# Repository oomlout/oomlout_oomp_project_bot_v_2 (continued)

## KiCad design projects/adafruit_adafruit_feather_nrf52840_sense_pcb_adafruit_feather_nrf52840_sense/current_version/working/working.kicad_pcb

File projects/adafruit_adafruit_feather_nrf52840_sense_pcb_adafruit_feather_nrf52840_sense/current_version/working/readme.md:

# adafruit_feather_nrf52840_sense_pcb
 
## summary 
* id: adafruit_adafruit_feather_nrf52840_sense_pcb_adafruit_feather_nrf52840_sense
* user: adafruit
* name: adafruit_feather_nrf52840_sense_pcb
* board: adafruit_feather_nrf52840_sense
* repo: https://github.com/adafruit/Adafruit-Feather-nRF52840-Sense-PCB

* src_file_repo_sch: 
* src_file_repo_sch_link: https://github.com/adafruit/Adafruit-Feather-nRF52840-Sense-PCB/tree/master/
* full details link: https://github.com/oomlout/oomlout_oomp_project_bot_v_2/tree/main/projects/adafruit_adafruit_feather_nrf52840_sense_pcb_adafruit_feather_nrf52840_sense/current_version/working  

## schematic  
  
[schematic (pdf)](working_schematic.pdf) 

## pcb  

[board (pdf)](working.pdf)  

## working_bom
| Id | Designator | Footprint | Quantity | Designation | Supplier and ref |  | None | 
| --- | --- | --- | --- | --- | --- | --- | --- | 
| 1 | R11,R10 | 0603-NO | 2 | 22 |  |  | [''] | 
| 2 | MDBT1 | MDBT50 | 1 | MDBT50 |  |  | [''] | 
| 3 | U3 | SOT23-5 | 1 | MCP73831T-2ACI/OT |  |  | [''] | 
| 4 | C7,C6,C5,C8,C9 | 0805-NO | 5 | 10uF |  |  | [''] | 
| 5 | U1 | APDS-9960 | 1 | APDS-9960 |  |  | [''] | 
| 6 | X2 | JSTPH2 | 1 | CON_JST_PH_2PIN_MTPH2 |  |  | [''] | 
| 7 | IC4 | SPK0415HM4H | 1 | MIC_PDM |  |  | [''] | 
| 8 | R1 | 0603-NO | 1 | 2.2K |  |  | [''] | 
| 9 | C10,C1,C3,C12,C13 | 0603-NO | 5 | 0.1uF |  |  | [''] | 
| 10 | D1 | SOD-123 | 1 | MBR054 |  |  | [''] | 
| 11 | R4 | 0603-NO | 1 | 4.7K |  |  | [''] | 
| 12 | D3 | CHIPLED_0805_NOOUTLINE | 1 | ORANGE |  |  | [''] | 
| 13 | L1 | _0805MP | 1 | DNP |  |  | [''] | 
| 14 | FID2,FID1 | FIDUCIAL_1MM | 2 | FIDUCIAL_1MM |  |  | [''] | 
| 15 | X1 | 4UCONN_20329_V2 | 1 | 4u20329 |  |  | [''] | 
| 16 | IC1 | LGA16_3X3MM | 1 | LSM6DS33 |  |  | [''] | 
| 17 | U$14 | FEATHERSENSE_TOP | 1 |  |  |  | [''] | 
| 18 | D2 | CHIPLED_0805_NOOUTLINE | 1 | RED |  |  | [''] | 
| 19 | C4 | 0603-NO | 1 | 1uF |  |  | [''] | 
| 20 | U5 | BMP280 | 1 | BMP280 |  |  | [''] | 
| 21 | U4 | SHT3X | 1 | SHT30 |  |  | [''] | 
| 22 | D4 | CHIPLED_0603_NOOUTLINE | 1 | BLUE |  |  | [''] | 
| 23 | SW1,SW2 | BTN_KMR2_4.6X2.8 | 2 | KMR2 |  |  | [''] | 
| 24 | LED1 | LED3535 | 1 | WS2812B3535 |  |  | [''] | 
| 25 | R7 | RESPACK_4X0603 | 1 | 4.7K |  |  | [''] | 
| 26 | Q3 | SOT23-R | 1 | DMG2305 |  |  | [''] | 
| 27 | U2 | SOT23-5 | 1 | AP2112(3.3V) |  |  | [''] | 
| 28 | R3 | 0603-NO | 1 | 1K |  |  | [''] | 
| 29 | IC3 | LGA12_2X2MM | 1 | LIS3MDL |  |  | [''] | 
| 30 | MS1 | FEATHERWING_NODIM | 1 | FEATHERWING_NODIM |  |  | [''] | 
| 31 | IC2 | USON8 | 1 | GD25Q16 |  |  | [''] | 
| 32 | R12 | RESPACK_4X0603 | 1 | 100K |  |  | [''] | 
| 33 | TP1,D-0,D+0 | TP10R | 3 | TPTP10R |  |  | [''] | 
| 34 | SWC0,SWD0 | TP12R | 2 | TPTP12R |  |  | [''] | 
| 35 | U$75 | FEATHERSENSE_BOT | 1 |  |  |  | [''] | 
| 36 | U$10 | PCBFEAT-REV-056 | 1 |  |  |  | [''] | 

## bom_schematic
| Ref | Qnty | Value | Cmp name | Footprint | Description | Vendor | DNP | 
| --- | --- | --- | --- | --- | --- | --- | --- | 
| C1, C3, C10, C12, C13 | 5 | 0.1uF | CAP_CERAMIC0603_NO | working:0603-NO |  |  |  | 
| C4 | 1 | 1uF | CAP_CERAMIC0603_NO | working:0603-NO |  |  |  | 
| C5, C6, C7, C8, C9 | 5 | 10uF | CAP_CERAMIC0805-NOOUTLINE | working:0805-NO |  |  |  | 
| D1 | 1 | MBR054 | DIODE-SCHOTTKYSOD-123 | working:SOD-123 |  |  |  | 
| D2 | 1 | RED | LED0805_NOOUTLINE | working:CHIPLED_0805_NOOUTLINE |  |  |  | 
| D3 | 1 | ORANGE | LED0805_NOOUTLINE | working:CHIPLED_0805_NOOUTLINE |  |  |  | 
| D4 | 1 | BLUE | LED0603_NOOUTLINE | working:CHIPLED_0603_NOOUTLINE |  |  |  | 
| D+0 | 1 | TPTP10R | TPTP10R | working:TP10R |  |  |  | 
| D-0 | 1 | TPTP10R | TPTP10R | working:TP10R |  |  |  | 
| FID1, FID2 | 2 | FIDUCIAL_1MM | FIDUCIAL_1MM | working:FIDUCIAL_1MM |  |  |  | 
| IC1 | 1 | LSM6DS33 | LSM6DS33 | working:LGA16_3X3MM |  |  |  | 
| IC2 | 1 | GD25Q16 | SPIFLASH_8PINUX | working:USON8 |  |  |  | 
| IC3 | 1 | LIS3MDL | LIS3MDL | working:LGA12_2X2MM |  |  |  | 
| IC4 | 1 | MIC_PDM_SPK0415 | MIC_PDM_SPK0415 | working:SPK0415HM4H |  |  |  | 
| L1 | 1 | DNP | INDUCTOR_0805MP | working:_0805MP |  |  |  | 
| LED1 | 1 | WS2812B3535 | WS2812B3535 | working:LED3535 |  |  |  | 
| MDBT1 | 1 | MDBT50 | MDBT50 | working:MDBT50 |  |  |  | 
| MS1 | 1 | FEATHERWING_NODIM | FEATHERWING_NODIM | working:FEATHERWING_NODIM |  |  |  | 
| Q3 | 1 | DMG2305 | MOSFET-P | working:SOT23-R |  |  |  | 
| R1 | 1 | 2.2K | RESISTOR_0603_NOOUT | working:0603-NO |  |  |  | 
| R3 | 1 | 1K | RESISTOR_0603_NOOUT | working:0603-NO |  |  |  | 
| R4 | 1 | 4.7K | RESISTOR_0603_NOOUT | working:0603-NO |  |  |  | 
| R7 | 1 | 4.7K | RESISTOR_4PACK | working:RESPACK_4X0603 |  |  |  | 
| R10, R11 | 2 | 22 | RESISTOR_0603_NOOUT | working:0603-NO |  |  |  | 
| R12 | 1 | 100K | RESISTOR_4PACK | working:RESPACK_4X0603 |  |  |  | 
| SW1, SW2 | 2 | KMR2 | SWITCH_TACT_SMT4.6X2.8 | working:BTN_KMR2_4.6X2.8 |  |  |  | 
| SWC0 | 1 | TPTP12R | TPTP12R | working:TP12R |  |  |  | 
| SWD0 | 1 | TPTP12R | TPTP12R | working:TP12R |  |  |  | 
| TP1 | 1 | TPTP10R | TPTP10R | working:TP10R |  |  |  | 
| U1 | 1 | APDS-9960 | APDS-9960 | working:APDS-9960 |  |  |  | 
| U2 | 1 | AP2112(3.3V) | VREG_SOT23-5 | working:SOT23-5 |  |  |  | 
| U3 | 1 | MCP73831T-2ACI/OT | MCP73831/2 | working:SOT23-5 |  |  |  | 
| U4 | 1 | SHT30 | SHT3X | working:SHT3X |  |  |  | 
| U5 | 1 | BMP280 | BMP280 | working:BMP280 |  |  |  | 
| X1 | 1 | 4u20329 | USB_MICRO_20329_V2 | working:4UCONN_20329_V2 |  |  |  | 
| X2 | 1 | CON_JST_PH_2PIN_MTPH2 | CON_JST_PH_2PIN_MTPH2 | working:JSTPH2 |  |  |  |

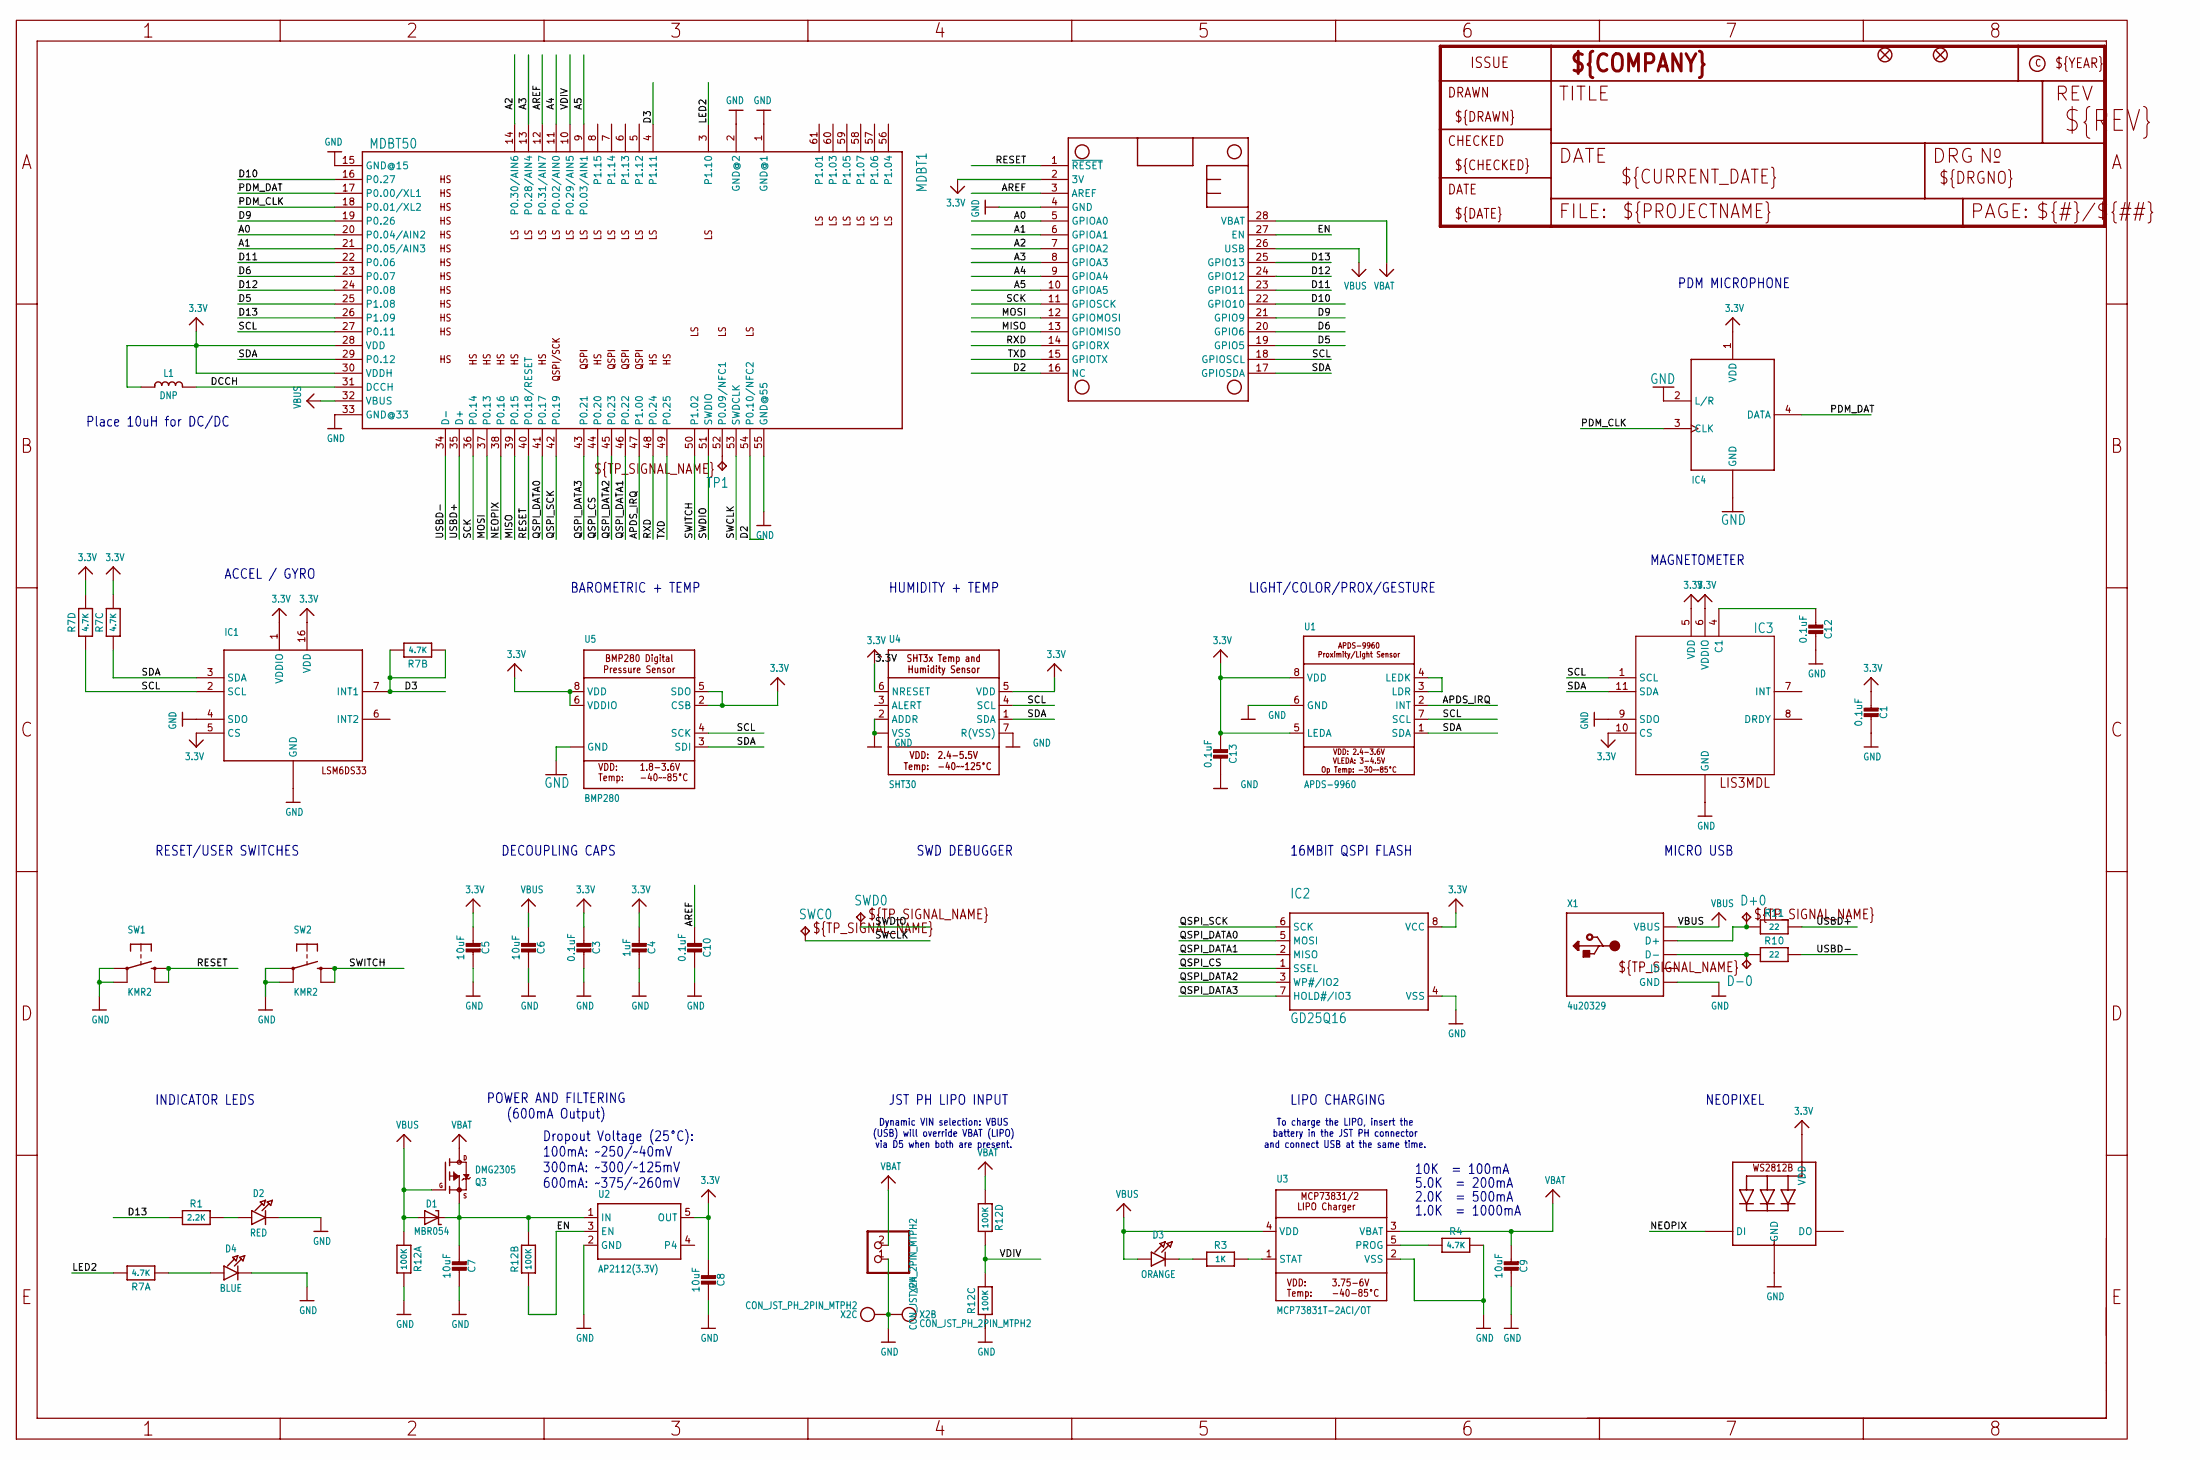
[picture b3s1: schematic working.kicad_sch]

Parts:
C1, C3, C10, C12, C13: 0.1uF; 0603-NO
C4: 1uF; 0603-NO
C5, C6, C7, C8, C9: 10uF; 0805-NO
D1: MBR054; SOD-123
D2: RED; CHIPLED_0805_NOOUTLINE
D3: ORANGE; CHIPLED_0805_NOOUTLINE
D4: BLUE; CHIPLED_0603_NOOUTLINE
D+0: TPTP10R; TP10R
D-0: TPTP10R; TP10R
FID1, FID2: FIDUCIAL_1MM
IC1: LSM6DS33; LGA16_3X3MM
IC2: GD25Q16; USON8
IC3: LIS3MDL; LGA12_2X2MM
IC4: MIC_PDM_SPK0415; SPK0415HM4H
L1: DNP; _0805MP
LED1: WS2812B3535; LED3535
MDBT1: MDBT50
MS1: FEATHERWING_NODIM
Q3: DMG2305; SOT23-R
R1: 2.2K; 0603-NO
R3: 1K; 0603-NO
R4: 4.7K; 0603-NO
R7: 4.7K; RESPACK_4X0603
R10, R11: 22; 0603-NO
R12: 100K; RESPACK_4X0603
SW1, SW2: KMR2; BTN_KMR2_4.6X2.8
SWC0: TPTP12R; TP12R
SWD0: TPTP12R; TP12R
TP1: TPTP10R; TP10R
U1: APDS-9960
U2: AP2112(3.3V); SOT23-5
U3: MCP73831T-2ACI/OT; SOT23-5
U4: SHT30; SHT3X
U5: BMP280
X1: 4u20329; 4UCONN_20329_V2
X2: CON_JST_PH_2PIN_MTPH2; JSTPH2

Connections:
3.3V: C1.2, C3.2, C4.2, C5.2, C8.2, C13.2, IC1.1 (VDDIO), IC1.5 (CS), IC1.16 (VDD), IC2.8 (VCC), IC3.5 (VDD), IC3.6 (VDDIO), IC3.10 (CS), IC4.1 (VDD), L1.1, LED1.2 (VDD), MDBT1.28 (VDD), MDBT1.30 (VDDH), MS1.2 (3V), R7.5 (2), R7.6 (2), U1.5 (LEDA), U1.8 (VDD), U2.5 (OUT), U4.5 (VDD), U4.6 (NRESET), U5.2 (CSB), U5.5 (SDO), U5.6 (VDDIO), U5.8 (VDD)
A0: MDBT1.20 (P0.04/AIN2), MS1.5 (GPIOA0)
A1: MDBT1.21 (P0.05/AIN3), MS1.6 (GPIOA1)
A2: MDBT1.14 (P0.30/AIN6), MS1.7 (GPIOA2)
A3: MDBT1.13 (P0.28/AIN4), MS1.8 (GPIOA3)
A4: MDBT1.11 (P0.02/AIN0), MS1.9 (GPIOA4)
A5: MDBT1.9 (P0.03/AIN1), MS1.10 (GPIOA5)
APDS_IRQ: MDBT1.47 (P1.00), U1.2 (INT)
AREF: C10.2, MDBT1.12 (P0.31/AIN7), MS1.3 (AREF)
CAP1: C12.2, IC3.4 (C1)
D2: MDBT1.54 (P0.10/NFC2), MS1.16 (NC)
D3: IC1.7 (INT1), MDBT1.4 (P1.11), R7.2 (1), R7.7 (2)
D5: MDBT1.25 (P1.08), MS1.19 (GPIO5)
D6: MDBT1.23 (P0.07), MS1.20 (GPIO6)
D9: MDBT1.19 (P0.26), MS1.21 (GPIO9)
D10: MDBT1.16 (P0.27), MS1.22 (GPIO10)
D11: MDBT1.22 (P0.06), MS1.23 (GPIO11)
D12: MDBT1.24 (P0.08), MS1.24 (GPIO12)
D13: MDBT1.26 (P1.09), MS1.25 (GPIO13), R1.1
D+: D+0.TP, R11.1, X1.D+
D-: D-0.TP, R10.1, X1.D-
DCCH: L1.2, MDBT1.31 (DCCH)
EN: MS1.27 (EN), R12.2 (1), U2.3 (EN)
GND: C1.1, C3.1, C4.1, C5.1, C6.1, C7.1, C8.1, C9.1, C10.1, C12.1, C13.1, D2.C, D4.C, IC1.4 (SDO), IC1.8 (GND), IC1.9 (GND), IC1.10 (GND), IC1.11 (GND), IC1.12 (GND), IC1.13 (GND), IC1.15 (GND), IC2.4 (VSS), IC3.2 (GND), IC3.3 (GND), IC3.9 (SDO), IC3.12 (GND), IC4.2 (L/R), IC4.5 (GND), IC4.6 (GND), IC4.7 (GND), IC4.8 (GND), LED1.4 (GND), MDBT1.1 (GND@1), MDBT1.2 (GND@2), MDBT1.15 (GND@15), MDBT1.33 (GND@33), MDBT1.55 (GND@55), MS1.4 (GND), R4.2, R12.3 (1), R12.8 (2), SW1.A, SW1.A' (P1), SW2.A, SW2.A' (P1), U1.6 (GND), U2.2 (GND), U3.2 (VSS), U4.2 (ADDR), U4.7 (R(VSS)), U4.8 (VSS), U4.THERMAL (VSS), U5.1 (GND), U5.7 (GND), X1.BASE@1 (GND), X1.BASE@2 (GND), X1.GND, X1.SPRT@1 (GND), X1.SPRT@2 (GND), X1.SPRT@3 (GND), X1.SPRT@4 (GND), X2.1, X2.NC1, X2.NC2
LED2: MDBT1.3 (P1.10), R7.8 (2)
MISO: MDBT1.39 (P0.15), MS1.13 (GPIOMISO)
MOSI: MDBT1.37 (P0.13), MS1.12 (GPIOMOSI)
unnamed: D3.C, R3.1
unnamed: U1.3 (LDR), U1.4 (LEDK)
unnamed: D4.A, R7.1
unnamed: D2.A, R1.2
unnamed: R3.2, U3.1 (STAT)
unnamed: R4.1, U3.5 (PROG)
NEOPIX: LED1.1 (DI), MDBT1.38 (P0.16)
NFC2: MDBT1.52 (P0.09/NFC1), TP1.TP
PDM_CLK: IC4.3 (CLK), MDBT1.18 (P0.01/XL2)
PDM_DAT: IC4.4 (DATA), MDBT1.17 (P0.00/XL1)
QSPI_CS: IC2.1 (SSEL), MDBT1.44 (P0.20)
QSPI_DATA0: IC2.5 (MOSI), MDBT1.41 (P0.17)
QSPI_DATA1: IC2.2 (MISO), MDBT1.46 (P0.22)
QSPI_DATA2: IC2.3 (WP#/IO2), MDBT1.45 (P0.23)
QSPI_DATA3: IC2.7 (HOLD#/IO3), MDBT1.43 (P0.21)
QSPI_SCK: IC2.6 (SCK), MDBT1.42 (P0.19)
RESET: MDBT1.40 (P0.18/RESET), MS1.1 (~RESET), SW1.B (S), SW1.B' (S1)
RXD: MDBT1.48 (P0.24), MS1.14 (GPIORX)
SCK: MDBT1.36 (P0.14), MS1.11 (GPIOSCK)
SCL: IC1.2 (SCL), IC3.1 (SCL), MDBT1.27 (P0.11), MS1.18 (GPIOSCL), R7.4 (1), U1.7 (SCL), U4.4 (SCL), U5.4 (SCK)
SDA: IC1.3 (SDA), IC3.11 (SDA), MDBT1.29 (P0.12), MS1.17 (GPIOSDA), R7.3 (1), U1.1 (SDA), U4.1 (SDA), U5.3 (SDI)
SWCLK: MDBT1.53 (SWDCLK), SWC0.TP
SWDIO: MDBT1.51 (SWDIO), SWD0.TP
SWITCH: MDBT1.50 (P1.02), SW2.B (S), SW2.B' (S1)
TXD: MDBT1.49 (P0.25), MS1.15 (GPIOTX)
USBD+: MDBT1.35 (D+), R11.2
USBD-: MDBT1.34 (D-), R10.2
VBAT: C9.2, MS1.28 (VBAT), Q3.3 (D), R12.4 (1), U3.3 (VBAT), X2.2
VBUS: C6.2, D1.A, D3.A, MDBT1.32 (VBUS), MS1.26 (USB), Q3.1 (G), R12.1, U3.4 (VDD), X1.VBUS
VDIV: MDBT1.10 (P0.29/AIN5), R12.5 (2), R12.6 (2)
VHI: C7.2, D1.C, Q3.2 (S), R12.7 (2), U2.1 (IN)

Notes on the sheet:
RESET/USER SWITCHES
HUMIDITY + TEMP
LIGHT/COLOR/PROX/GESTURE
ACCEL / GYRO
2.0K = 500mA
Place 10uH for DC/DC
1.0K = 1000mA
To charge the LIPO, insert the battery in the JST PH connector and connect USB at the same time.
JST PH LIPO INPUT
Dropout Voltage (25°C): 100mA: ~250/~40mV 300mA: ~300/~125mV 600mA: ~375/~260mV
SWD DEBUGGER
DECOUPLING CAPS
LIPO CHARGING
5.0K = 200mA
INDICATOR LEDS
10K = 100mA
PDM MICROPHONE
BAROMETRIC + TEMP
MAGNETOMETER
MICRO USB
NEOPIXEL
POWER AND FILTERING (600mA Output)
Dynamic VIN selection: VBUS (USB) will override VBAT (LIPO) via D5 when both are present.
16MBIT QSPI FLASH

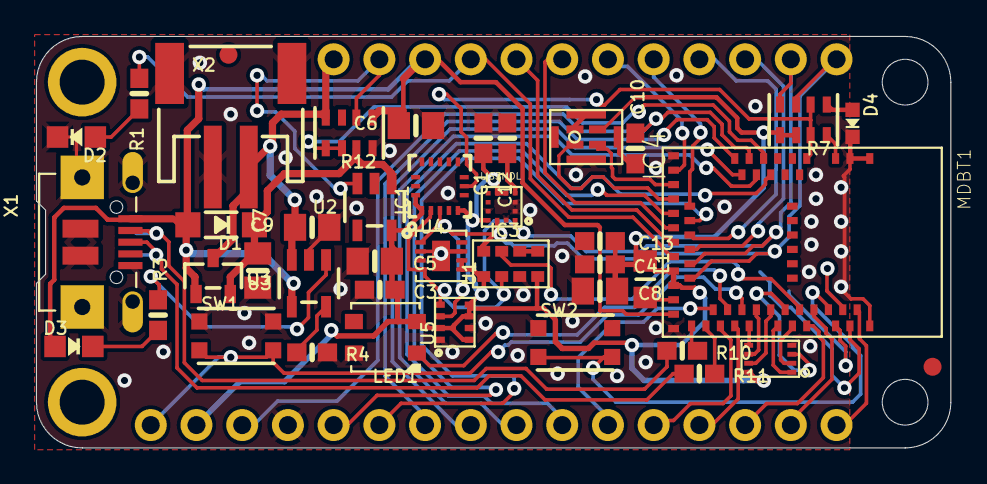
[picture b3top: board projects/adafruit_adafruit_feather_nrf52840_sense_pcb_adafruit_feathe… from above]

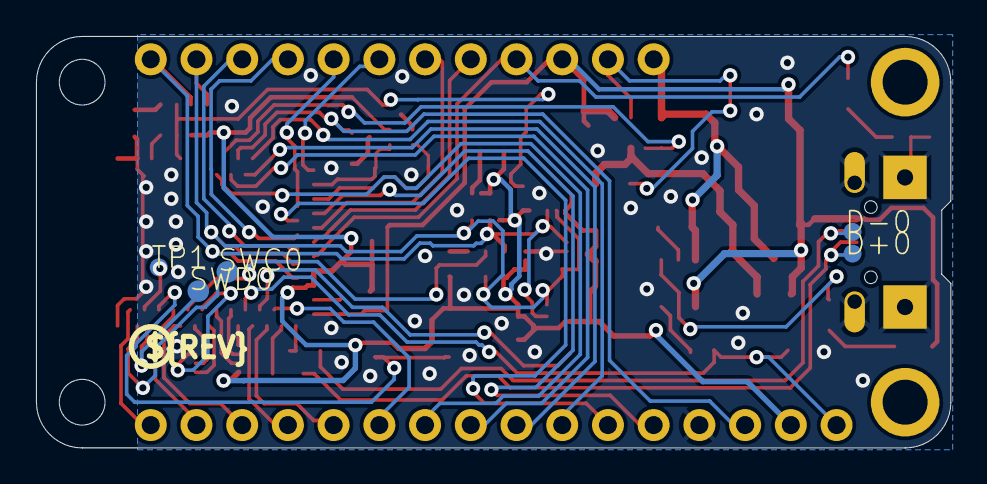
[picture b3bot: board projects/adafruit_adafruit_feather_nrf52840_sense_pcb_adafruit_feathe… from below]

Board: 4 copper layers, 50.8 x 22.9 mm, 50 parts (7 on the bottom side), 58 nets.

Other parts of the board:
U$10: PCBFEAT-REV-056
U$14: FEATHERSENSE_TOP
U$75: FEATHERSENSE_BOT

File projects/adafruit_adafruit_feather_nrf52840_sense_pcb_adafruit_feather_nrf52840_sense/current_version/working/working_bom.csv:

"Id";"Designator";"Footprint";"Quantity";"Designation";"Supplier and ref";
1;"R11,R10";"0603-NO";2;"22";;;
2;"MDBT1";"MDBT50";1;"MDBT50";;;
3;"U3";"SOT23-5";1;"MCP73831T-2ACI/OT";;;
4;"C7,C6,C5,C8,C9";"0805-NO";5;"10uF";;;
5;"U1";"APDS-9960";1;"APDS-9960";;;
6;"X2";"JSTPH2";1;"CON_JST_PH_2PIN_MTPH2";;;
7;"IC4";"SPK0415HM4H";1;"MIC_PDM";;;
8;"R1";"0603-NO";1;"2.2K";;;
9;"C10,C1,C3,C12,C13";"0603-NO";5;"0.1uF";;;
10;"D1";"SOD-123";1;"MBR054";;;
11;"R4";"0603-NO";1;"4.7K";;;
12;"D3";"CHIPLED_0805_NOOUTLINE";1;"ORANGE";;;
13;"L1";"_0805MP";1;"DNP";;;
14;"FID2,FID1";"FIDUCIAL_1MM";2;"FIDUCIAL_1MM";;;
15;"X1";"4UCONN_20329_V2";1;"4u20329";;;
16;"IC1";"LGA16_3X3MM";1;"LSM6DS33";;;
17;"U$14";"FEATHERSENSE_TOP";1;"";;;
18;"D2";"CHIPLED_0805_NOOUTLINE";1;"RED";;;
19;"C4";"0603-NO";1;"1uF";;;
20;"U5";"BMP280";1;"BMP280";;;
21;"U4";"SHT3X";1;"SHT30";;;
22;"D4";"CHIPLED_0603_NOOUTLINE";1;"BLUE";;;
23;"SW1,SW2";"BTN_KMR2_4.6X2.8";2;"KMR2";;;
24;"LED1";"LED3535";1;"WS2812B3535";;;
25;"R7";"RESPACK_4X0603";1;"4.7K";;;
26;"Q3";"SOT23-R";1;"DMG2305";;;
27;"U2";"SOT23-5";1;"AP2112(3.3V)";;;
28;"R3";"0603-NO";1;"1K";;;
29;"IC3";"LGA12_2X2MM";1;"LIS3MDL";;;
30;"MS1";"FEATHERWING_NODIM";1;"FEATHERWING_NODIM";;;
31;"IC2";"USON8";1;"GD25Q16";;;
32;"R12";"RESPACK_4X0603";1;"100K";;;
33;"TP1,D-0,D+0";"TP10R";3;"TPTP10R";;;
34;"SWC0,SWD0";"TP12R";2;"TPTP12R";;;
35;"U$75";"FEATHERSENSE_BOT";1;"";;;
36;"U$10";"PCBFEAT-REV-056";1;"";;;

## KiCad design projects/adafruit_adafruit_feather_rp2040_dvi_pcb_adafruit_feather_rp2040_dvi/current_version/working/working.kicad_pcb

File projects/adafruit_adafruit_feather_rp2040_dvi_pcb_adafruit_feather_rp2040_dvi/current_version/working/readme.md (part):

# adafruit_feather_rp2040_dvi_pcb
 
## summary 
* id: adafruit_adafruit_feather_rp2040_dvi_pcb_adafruit_feather_rp2040_dvi
* user: adafruit
* name: adafruit_feather_rp2040_dvi_pcb
* board: adafruit_feather_rp2040_dvi
* repo: https://github.com/adafruit/Adafruit-Feather-RP2040-DVI-PCB

* src_file_repo_sch: 
* src_file_repo_sch_link: https://github.com/adafruit/Adafruit-Feather-RP2040-DVI-PCB/tree/main/
* full details link: https://github.com/oomlout/oomlout_oomp_project_bot_v_2/tree/main/projects/adafruit_adafruit_feather_rp2040_dvi_pcb_adafruit_feather_rp2040_dvi/current_version/working  

## schematic  
  
[schematic (pdf)](working_schematic.pdf) 

## pcb  

[board (pdf)](working.pdf)  

## working_bom
| Id | Designator | Footprint | Quantity | Designation | Supplier and ref |  | None | 
| --- | --- | --- | --- | --- | --- | --- | --- | 
| 1 | LED1 | SK6805_1515 | 1 | WS2812B_SK6805_1515 |  |  | [''] | 
| 2 | PLABEL25 | PLABEL25 | 1 |  |  |  | [''] | 
| 3 | PLABEL9 | PLABEL9 | 1 |  |  |  | [''] | 
| 4 | PLABEL23 | PLABEL23 | 1 |  |  |  | [''] | 
| 5 | C13,C18,C14,C6,C12,C9,C7 | _0402NO | 7 | 0.1uF |  |  | [''] | 
| 6 | D3 | SOD-323F | 1 | 1N4148 |  |  | [''] | 
| 7 | PLABEL12 | PLABEL12 | 1 |  |  |  | [''] | 
| 8 | R20,R18,R3,R7,R19,R1,R2,R4,R5,R21 | _0402NO | 10 | 10K |  |  | [''] | 
| 9 | R10,R9 | _0402NO | 2 | 22 ohm |  |  | [''] | 
| 10 | C5,C1,C4,C20,C19 | 0805-NO | 5 | 10uF |  |  | [''] | 
| 11 | SW1,SW2 | BTN_RKB2_4.6X2.8 | 2 | KMR2 |  |  | [''] | 
| 12 | C10,C17,C11,C15,C21,C8 | _0402NO | 6 | 1uF |  |  | [''] | 
| 13 | PLABEL22 | PLABEL22 | 1 |  |  |  | [''] | 
| 14 | PLABEL29 | PLABEL29 | 1 |  |  |  | [''] | 
| 15 | PLABEL30 | PLABEL30 | 1 |  |  |  | [''] | 
| 16 | PLABEL32 | PLABEL32 | 1 |  |  |  | [''] | 
| 17 | U$31,U$32 | MOUNTINGHOLE_2.5_PLATED | 2 | MOUNTINGHOLE2.5 |  |  | [''] | 
| 18 | D4 | SOD-323F | 1 | PMEG2020AEA |  |  | [''] | 
| 19 | UTIL0,CEC0 | 1X01_ROUND | 2 |  |  |  | [''] | 
| 20 | PLABEL31 | PLABEL31 | 1 |  |  |  | [''] | 
| 21 | R14,R15 | RESPACK_4X0603 | 2 | 220 Pack |  |  | [''] | 
| 22 | PLABEL35 | PLABEL35 | 1 |  |  |  | [''] | 
| 23 | JP3 | 1X12_ROUND | 1 |  |  |  | [''] | 
| 24 | R8,R13,R12 | _0402NO | 3 | 5.1K |  |  | [''] | 
| 25 | @HOLE0,@HOLE1 |  | 2 |  |  |  | [''] | 
| 26 | PLABEL27 | PLABEL27 | 1 |  |  |  | [''] | 
| 27 | PLABEL11 | PLABEL11 | 1 |  |  |  | [''] | 
| 28 | PLABEL4 | PLABEL4 | 1 |  |  |  | [''] | 
| 29 | U2 | SOT23-5 | 1 | RT9080-3.3 |  |  | [''] | 
| 30 | PLABEL5 | PLABEL5 | 1 |  |  |  | [''] | 
| 31 | PLABEL19 | PLABEL19 | 1 |  |  |  | [''] | 
| 32 | PLABEL28 | PLABEL28 | 1 |  |  |  | [''] | 
| 33 | PLABEL33 | PLABEL33 | 1 |  |  |  | [''] | 
| 34 | L0 | CHIPLED_0603_NOOUTLINE | 1 | RED |  |  | [''] | 
| 35 | PLABEL2 | PLABEL2 | 1 |  |  |  | [''] | 
| 36 | PLABEL3 | PLABEL3 | 1 |  |  |  | [''] | 
| 37 | PLABEL20 | PLABEL20 | 1 |  |  |  | [''] | 
| 38 | PLABEL34 | PLABEL34 | 1 |  |  |  | [''] | 
| 39 | PLABEL14 | PLABEL14 | 1 |  |  |  | [''] | 
| 40 | PLABEL17 | PLABEL17 | 1 |  |  |  | [''] | 
| 41 | R11,R6 | _0402NO | 2 | 1K |  |  | [''] | 
| 42 | PLABEL0 | PLABEL0 | 1 |  |  |  | [''] | 
| 43 | C2,C3 | _0402NO | 2 | 22pF |  |  | [''] | 
| 44 | R16,R17 | _0402NO | 2 | 100K |  |  | [''] | 
| 45 | PLABEL13 | PLABEL13 | 1 |  |  |  | [''] | 
| 46 | PLABEL8 | PLABEL8 | 1 |  |  |  | [''] | 
| 47 | U$35,U$34 | FIDUCIAL_1MM | 2 | FIDUCIAL_1MM |  |  | [''] | 
| 48 | X2 | HDMI_MOLEX_47151-0001 | 1 | 47151-0001 |  |  | [''] | 
| 49 | PLABEL1 | PLABEL1 | 1 |  |  |  | [''] | 
| 50 | PLABEL21 | PLABEL21 | 1 |  |  |  | [''] | 
| 51 | U3 | SOT23-5 | 1 | MCP73831T-2ACI/OT |  |  | [''] | 
| 52 | CONN1 | JST_SH4_RA | 1 | STEMMA_I2C_QTRA |  |  | [''] | 
| 53 | Q2 | SOT363 | 1 | BSS138 |  |  | [''] | 
| 54 | Y1 | CRYSTAL_2.5X2 | 1 | 12MHz/12pF |  |  | [''] | 
| 55 | JP1 | 1X16_ROUND | 1 |  |  |  | [''] | 
| 56 | PLABEL15 | PLABEL15 | 1 |  |  |  | [''] | 
| 57 | Q3 | DFN2015-3 | 1 | DMG3415UFY |  |  | [''] | 
| 58 | IC1 | QFN56_7MM_REDUCEDEPAD | 1 | RP2040_QFN56 |  |  | [''] | 
| 59 | PLABEL24 | PLABEL24 | 1 |  |  |  | [''] | 
| 60 | PLABEL18 | PLABEL18 | 1 |  |  |  | [''] | 
| 61 | PLABEL6 | PLABEL6 | 1 |  |  |  | [''] | 
| 62 | PLABEL10 | PLABEL10 | 1 |  |  |  | [''] | 
| 63 | U1 | USON8_4X4 | 1 | 8MB QSPI |  |  | [''] | 
| 64 | PLABEL7 | PLABEL7 | 1 |  |  |  | [''] | 
| 65 | X6 | USB_C_CUSB31-CFM2AX-01-X | 1 | USB Type C |  |  | [''] | 
| 66 | PLABEL26 | PLABEL26 | 1 |  |  |  | [''] | 
| 67 | PLABEL16 | PLABEL16 | 1 |  |  |  | [''] | 
| 68 | X1 | JSTPH2_BATT | 1 | JSTPH |  |  | [''] | 
| 69 | CHG0 | CHIPLED_0603_NOOUTLINE | 1 | ORANGE |  |  | [''] | 
| 70 | PLABEL49 | PLABEL49 | 1 |  |  |  | [''] | 
| 71 | PLABEL59 | PLABEL59 | 1 |  |  |  | [''] | 
| 72 | PLABEL51 | PLABEL51 | 1 |  |  |  | [''] | 
| 73 | PLABEL40 | PLABEL40 | 1 |  |  |  | [''] | 
| 74 | PLABEL61 | PLABEL61 | 1 |  |  |  | [''] | 
| 75 | PLABEL44 | PLABEL44 | 1 |  |  |  | [''] | 
| 76 | PLABEL65 | PLABEL65 | 1 |  |  |  | [''] | 
| 77 | PLABEL58 | PLABEL58 | 1 |  |  |  | [''] | 
| 78 | PLABEL36 | PLABEL36 | 1 |  |  |  | [''] | 
| 79 | PLABEL67 | PLABEL67 | 1 |  |  |  | [''] | 
| 80 | U$42 | FEATHERLOGO_MED | 1 |  |  |  | [''] | 
| 81 | PLABEL37 | PLABEL37 | 1 |  |  |  | [''] | 
| 82 | PLABEL56 | PLABEL56 | 1 |  |  |  | [''] | 
| 83 | PLABEL60 | PLABEL60 | 1 |  |  |  | [''] | 
| 84 | D+1,D-1 | B1,27 | 2 | TPB1,27 |  |  | [''] | 
| 85 | PLABEL66 | PLABEL66 | 1 |  |  |  | [''] | 
| 86 | PLABEL62 | PLABEL62 | 1 |  |  |  | [''] | 
| 87 | PLABEL45 | PLABEL45 | 1 |  |  |  | [''] | 
| 88 | PLABEL54 | PLABEL54 | 1 |  |  |  | [''] | 
| 89 | PLABEL48 | PLABEL48 | 1 |  |  |  | [''] | 
| 90 | PLABEL38 | PLABEL38 | 1 |  |  |  | [''] | 
| 91 | U$13 | PCBFEAT-REV-040 | 1 |  |  |  | [''] | 
| 92 | PLABEL42 | PLABEL42 | 1 |  |  |  | [''] | 
| 93 | U$46 | ADAFRUIT_5MM | 1 |  |  |  | [''] | 
| 94 | PLABEL50 | PLABEL50 | 1 |  |  |  | [''] | 
| 95 | PLABEL57 | PLABEL57 | 1 |  |  |  | [''] | 
| 96 | TP3 | TESTPOINT_ROUND_1.5MM_NO | 1 |  |  |  | [''] | 
| 97 | PLABEL55 | PLABEL55 | 1 |  |  |  | [''] | 
| 98 | PLABEL46 | PLABEL46 | 1 |  |  |  | [''] | 
| 99 | PLABEL64 | PLABEL64 | 1 |  |  |  | [''] | 
| 100 | PLABEL47 | PLABEL47 | 1 |  |  |  | [''] | 
| 101 | PLABEL53 | PLABEL53 | 1 |  |  |  | [''] | 
| 102 | PLABEL39 | PLABEL39 | 1 |  |  |  | [''] | 
| 103 | PLABEL52 | PLABEL52 | 1 |  |  |  | [''] | 
| 104 | PLABEL43 | PLABEL43 | 1 |  |  |  | [''] | 
| 105 | PLABEL63 | PLABEL63 | 1 |  |  |  | [''] | 
| 106 | PLABEL41 | PLABEL41 | 1 |  |  |  | [''] | 

## bom_schematic
| Ref | Qnty | Value | Cmp name | Footprint | Description | Vendor | DNP | 
| --- | --- | --- | --- | --- | --- | --- | --- | 
| C1, C4, C5, C19, C20 | 5 | 10uF | CAP_CERAMIC0805-NOOUTLINE | working:0805-NO |  |  |  | 
| C2, C3 | 2 | 22pF | CAP_CERAMIC_0402NO | working:_0402NO |  |  |  | 
| C6, C7, C9, C12, C13, C14, C18 | 7 | 0.1uF | CAP_CERAMIC_0402NO | working:_0402NO |  |  |  | 
| C8, C10, C11, C15, C17, C21 | 6 | 1uF | CAP_CERAMIC_0402NO | working:_0402NO |  |  |  | 
| CEC0 | 1 | HEADER-1X1ROUND | HEADER-1X1ROUND | working:1X01_ROUND |  |  |  | 
| CHG0 | 1 | ORANGE | LED0603_NOOUTLINE | working:CHIPLED_0603_NOOUTLINE |  |  |  | 
| CONN1 | 1 | STEMMA_I2C_QTRA | STEMMA_I2C_QTRA | working:JST_SH4_RA |  |  |  | 
| D3 | 1 | 1N4148 | DIODESOD-323F | working:SOD-323F |  |  |  | 
| D4 | 1 | PMEG2020AEA | DIODESOD-323F | working:SOD-323F |  |  |  | 
| D+1 | 1 | TPB1,27 | TPB1,27 | working:B1,27 |  |  |  | 
| D-1 | 1 | TPB1,27 | TPB1,27 | working:B1,27 |  |  |  | 
| IC1 | 1 | RP2040_QFN56 | RP2040_QFN56 | working:QFN56_7MM_REDUCEDEPAD |  |  |  | 
| JP1 | 1 | HEADER-1X16ROUND | HEADER-1X16ROUND | working:1X16_ROUND |  |  |  | 
| JP3 | 1 | HEADER-1X12 | HEADER-1X12 | working:1X12_ROUND |  |  |  | 
| L0 | 1 | RED | LED0603_NOOUTLINE | working:CHIPLED_0603_NOOUTLINE |  |  |  | 
| LED1 | 1 | WS2812B_SK6805_1515 | WS2812B_SK6805_1515 | working:SK6805_1515 |  |  |  | 
| Q2 | 1 | BSS138 | MOSFET-N_DUAL | working:SOT363 |  |  |  | 
| Q3 | 1 | DMG3415UFY | MOSFET-P_DFN2015 | working:DFN2015-3 |  |  |  | 
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
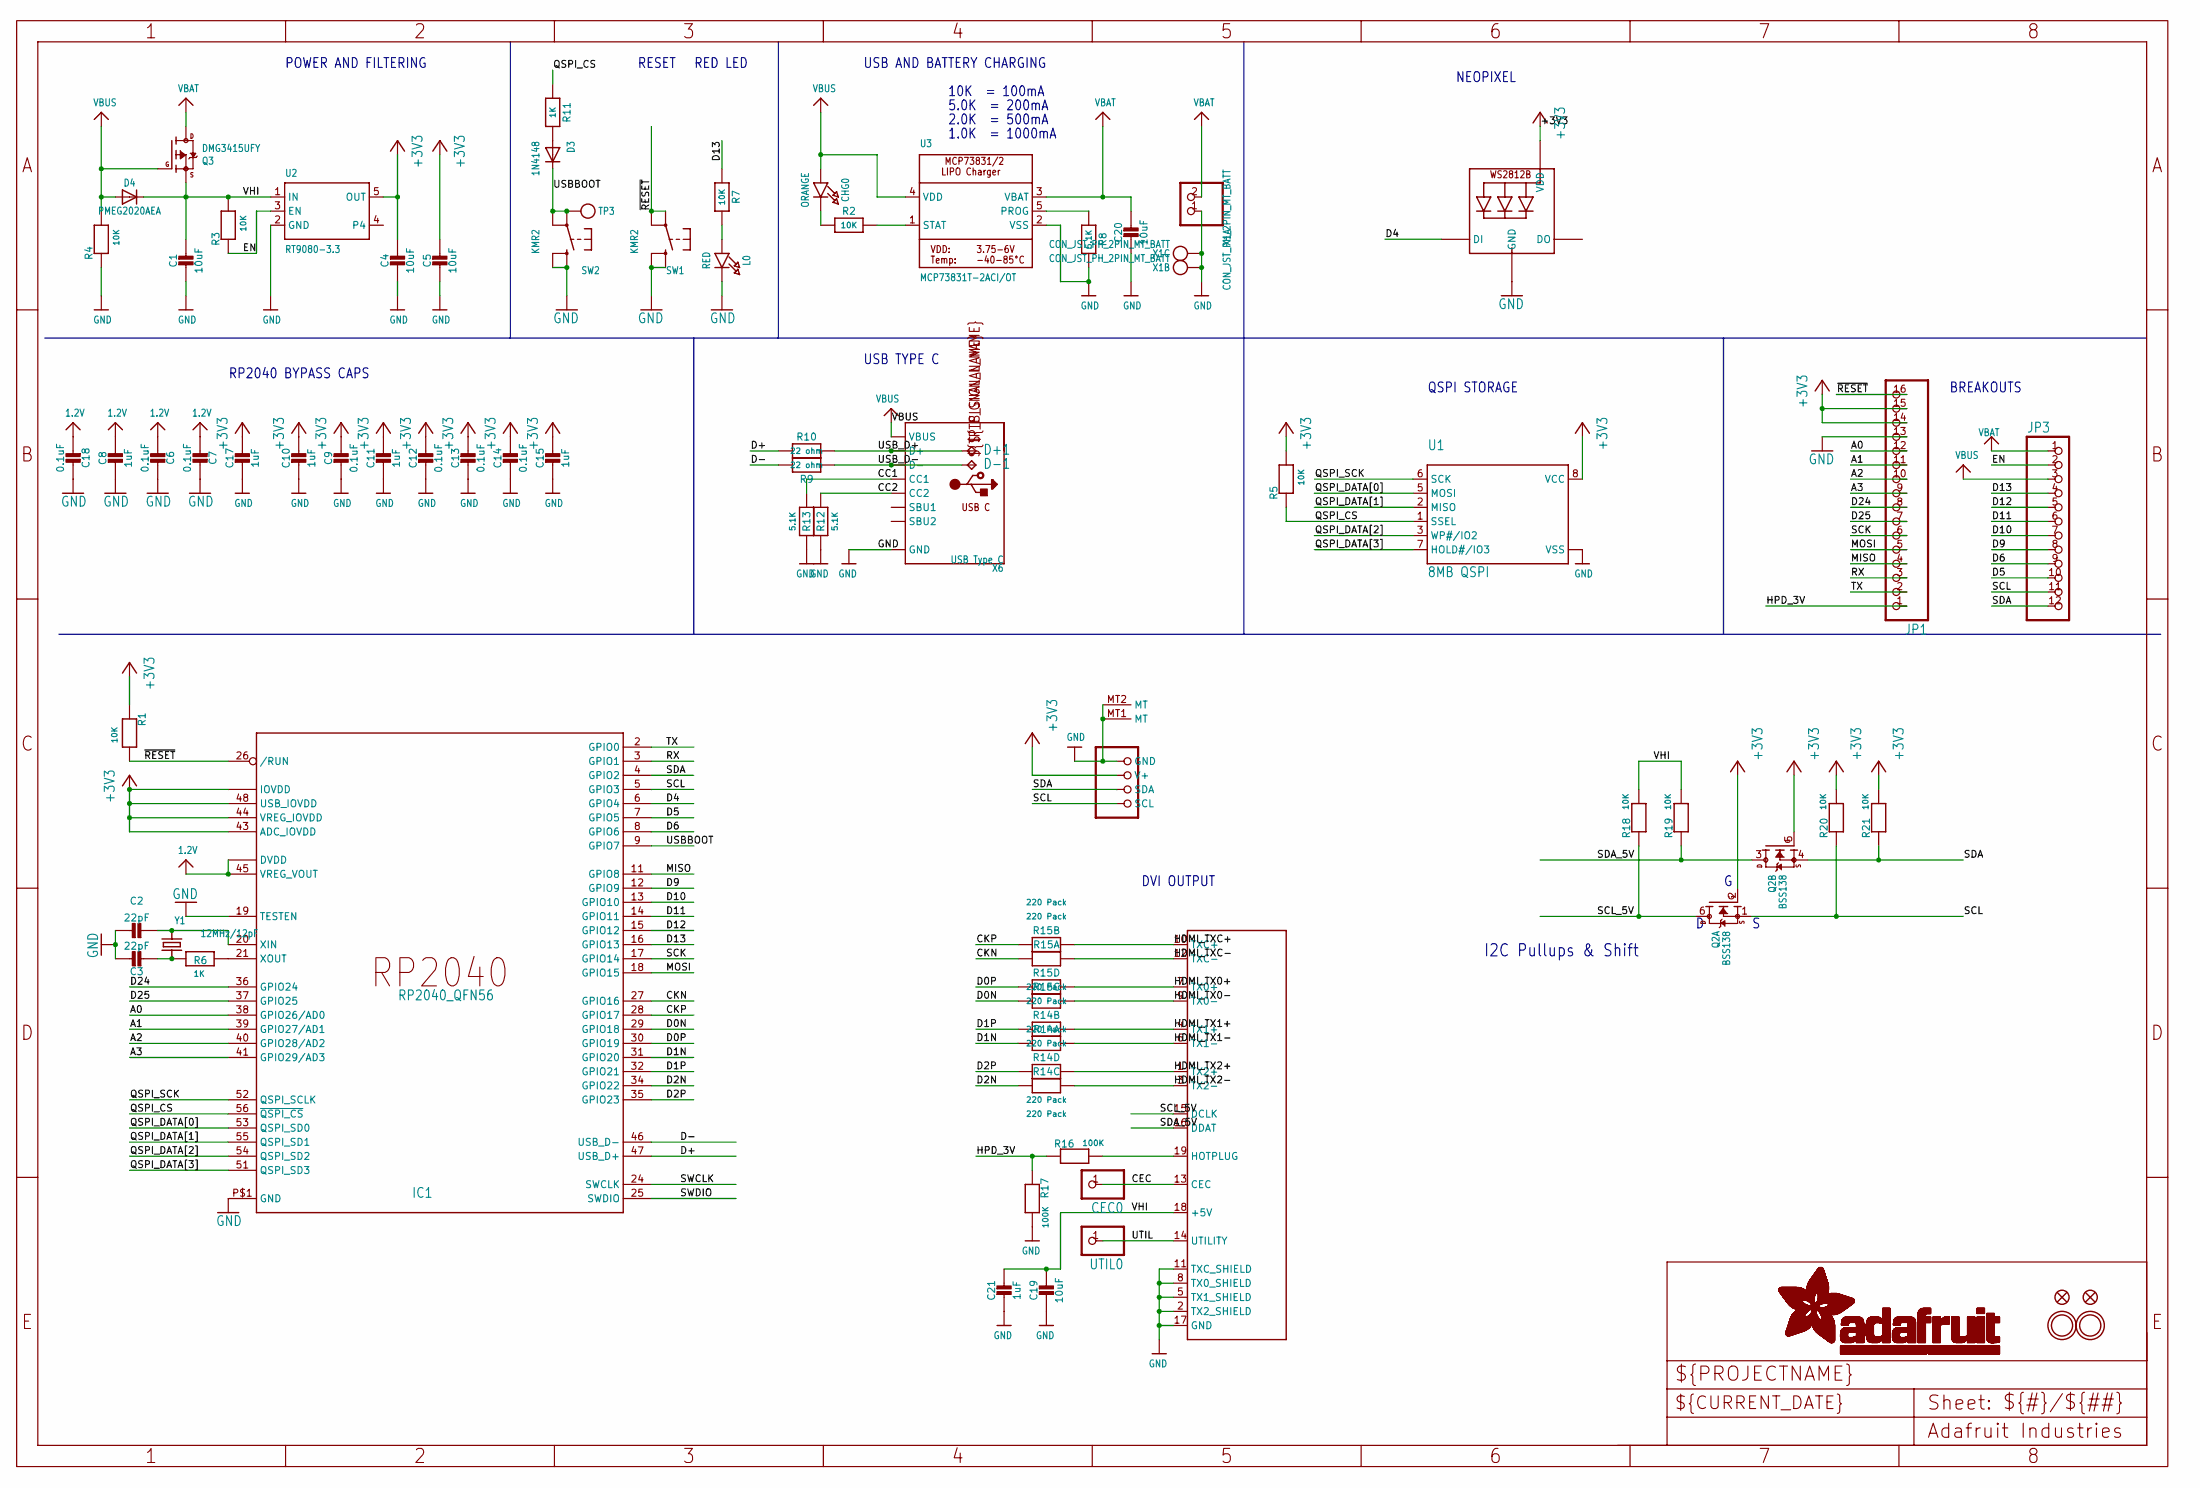
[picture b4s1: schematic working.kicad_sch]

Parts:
C1, C4, C5, C19, C20: 10uF; 0805-NO
C2, C3: 22pF; _0402NO
C6, C7, C9, C12, C13, C14, C18: 0.1uF; _0402NO
C8, C10, C11, C15, C17, C21: 1uF; _0402NO
CEC0: HEADER-1X1ROUND; 1X01_ROUND
CHG0: ORANGE; CHIPLED_0603_NOOUTLINE
CONN1: STEMMA_I2C_QTRA; JST_SH4_RA
D3: 1N4148; SOD-323F
D4: PMEG2020AEA; SOD-323F
D+1: TPB1,27; B1,27
D-1: TPB1,27; B1,27
IC1: RP2040_QFN56; QFN56_7MM_REDUCEDEPAD
JP1: HEADER-1X16ROUND; 1X16_ROUND
JP3: HEADER-1X12; 1X12_ROUND
L0: RED; CHIPLED_0603_NOOUTLINE
LED1: WS2812B_SK6805_1515; SK6805_1515
Q2: BSS138; SOT363
Q3: DMG3415UFY; DFN2015-3
R1, R2, R3, R4, R5, R7, R18, R19, R20, R21: 10K; _0402NO
R6, R11: 1K; _0402NO
R8, R12, R13: 5.1K; _0402NO
R9, R10: 22 ohm; _0402NO
R14, R15: 220 Pack; RESPACK_4X0603
R16, R17: 100K; _0402NO
SW1, SW2: KMR2; BTN_RKB2_4.6X2.8
TP3: TESTPOINTROUND1.5MMNO; TESTPOINT_ROUND_1.5MM_NO
U1: 8MB QSPI; USON8_4X4
U2: RT9080-3.3; SOT23-5; JLC_ROTATION 0
U3: MCP73831T-2ACI/OT; SOT23-5
U$31, U$32: MOUNTINGHOLE2.5; MOUNTINGHOLE_2.5_PLATED
U$34, U$35: FIDUCIAL_1MM
UTIL0: HEADER-1X1ROUND; 1X01_ROUND
X1: CON_JST_PH_2PIN_MT_BATT; JSTPH2_BATT
X2: 47151-0001; HDMI_MOLEX_47151-0001
X6: USB Type C; USB_C_CUSB31-CFM2AX-01-X
Y1: 12MHz/12pF; CRYSTAL_2.5X2

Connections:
1.2V: C6.2, C7.2, C8.1, C18.2, IC1.23 (DVDD), IC1.45 (VREG_VOUT), IC1.50 (DVDD)
+3V3: C4.1, C5.1, C9.1, C10.1, C11.1, C12.1, C13.1, C14.1, C15.1, C17.1, CONN1.2 (V+), IC1.1 (IOVDD), IC1.10 (IOVDD), IC1.22 (IOVDD), IC1.33 (IOVDD), IC1.42 (IOVDD), IC1.43 (ADC_IOVDD), IC1.44 (VREG_IOVDD), IC1.48 (USB_IOVDD), IC1.49 (IOVDD), JP1.14, JP1.15, LED1.2 (VDD), Q2.2 (G), Q2.5 (G), R1.1, R5.2, R20.2, R21.2, U1.8 (VCC), U2.5 (OUT)
A0: IC1.38 (GPIO26/AD0), JP1.12
A1: IC1.39 (GPIO27/AD1), JP1.11
A2: IC1.40 (GPIO28/AD2), JP1.10
A3: IC1.41 (GPIO29/AD3), JP1.9
CC1: R13.2, X6.A5 (CC1)
CC2: R12.2, X6.B5 (CC2)
CEC: CEC0.1, X2.13 (CEC)
CKN: IC1.27 (GPIO16), R15.8 (2)
CKP: IC1.28 (GPIO17), R15.7 (2)
D0N: IC1.29 (GPIO18), R15.6 (2)
D0P: IC1.30 (GPIO19), R15.5 (2)
D1N: IC1.31 (GPIO20), R14.8 (2)
D1P: IC1.32 (GPIO21), R14.7 (2)
D2N: IC1.34 (GPIO22), R14.6 (2)
D2P: IC1.35 (GPIO23), R14.5 (2)
D4: IC1.6 (GPIO4), LED1.1 (DI)
D5: IC1.7 (GPIO5), JP3.10
D6: IC1.8 (GPIO6), JP3.9
D9: IC1.12 (GPIO9), JP3.8
D10: IC1.13 (GPIO10), JP3.7
D11: IC1.14 (GPIO11), JP3.6
D12: IC1.15 (GPIO12), JP3.5
D13: IC1.16 (GPIO13), JP3.4, R7.1
D24: IC1.36 (GPIO24), JP1.8
D25: IC1.37 (GPIO25), JP1.7
D+: IC1.47 (USB_D+), R10.2
D-: IC1.46 (USB_D-), R9.2
EN: JP3.2, R3.1, U2.3 (EN)
GND: C1.2, C2.1, C3.1, C4.2, C5.2, C6.1, C7.1, C8.2, C9.2, C10.2, C11.2, C12.2, C13.2, C14.2, C15.2, C17.2, C18.1, C19.2, C20.2, C21.2, CONN1.1 (GND), CONN1.MT1 (MT), CONN1.MT2 (MT), IC1.19 (TESTEN), IC1.P$1 (GND), JP1.13, L0.C, LED1.4 (GND), R4.1, R8.2, R12.1, R13.1, R17.2, SW1.B (S), SW1.B' (S1), SW2.B (S), SW2.B' (S1), U1.4 (VSS), U1.PAD (VSS), U2.2 (GND), U3.2 (VSS), X1.1, X1.NC1, X1.NC2, X2.2 (TX2_SHIELD), X2.5 (TX1_SHIELD), X2.8 (TX0_SHIELD), X2.11 (TXC_SHIELD), X2.17 (GND), X2.P$1 (GND@1), X2.P$2 (GND@2), X2.P$3 (GND@3), X2.P$4 (GND@4), X6.A1B12 (GND), X6.B1A12 (GND)
HDMI_TX0+: R15.4 (1), X2.7 (TX0+)
HDMI_TX0-: R15.3 (1), X2.9 (TX0-)
HDMI_TX1+: R14.2 (1), X2.4 (TX1+)
HDMI_TX1-: R14.1, X2.6 (TX1-)
HDMI_TX2+: R14.4 (1), X2.1 (TX2+)
HDMI_TX2-: R14.3 (1), X2.3 (TX2-)
HDMI_TXC+: R15.2 (1), X2.10 (TXC+)
HDMI_TXC-: R15.1, X2.12 (TXC-)
HPD: R16.2, X2.19 (HOTPLUG)
HPD_3V: JP1.1, R16.1, R17.1
MISO: IC1.11 (GPIO8), JP1.4
MOSI: IC1.18 (GPIO15), JP1.5
unnamed: CHG0.C, R2.1
unnamed: L0.A, R7.2
unnamed: R2.2, U3.1 (STAT)
unnamed: R8.1, U3.5 (PROG)
unnamed: C2.2, IC1.20 (XIN), Y1.3 (2)
unnamed: C3.2, R6.1, Y1.1
unnamed: IC1.21 (XOUT), R6.2
unnamed: D3.A, R11.2
QSPI_CS: IC1.56 (~QSPI_CS), R5.1, R11.1, U1.1 (SSEL)
QSPI_DATA[0]: IC1.53 (QSPI_SD0), U1.5 (MOSI)
QSPI_DATA[1]: IC1.55 (QSPI_SD1), U1.2 (MISO)
QSPI_DATA[2]: IC1.54 (QSPI_SD2), U1.3 (WP#/IO2)
QSPI_DATA[3]: IC1.51 (QSPI_SD3), U1.7 (HOLD#/IO3)
QSPI_SCK: IC1.52 (QSPI_SCLK), U1.6 (SCK)
RX: IC1.3 (GPIO1), JP1.3
SCK: IC1.17 (GPIO14), JP1.6
SCL: CONN1.4 (SCL), IC1.5 (GPIO3), JP3.11, Q2.1 (S), R20.1
SCL_5V: Q2.6 (D), R18.1, X2.15 (DCLK)
SDA: CONN1.3 (SDA), IC1.4 (GPIO2), JP3.12, Q2.4 (S), R21.1
SDA_5V: Q2.3 (D), R19.1, X2.16 (DDAT)
SWCLK: IC1.24 (SWCLK)
SWDIO: IC1.25 (SWDIO)
TX: IC1.2 (GPIO0), JP1.2
USBBOOT: D3.C, IC1.9 (GPIO7), SW2.A, SW2.A' (P1), TP3.P$1
USB_D+: D+1.TP, R10.1, X6.A6 (D+), X6.B6 (D+)
USB_D-: D-1.TP, R9.1, X6.A7 (D-), X6.B7 (D-)
UTIL: UTIL0.1, X2.14 (UTILITY)
VBAT: C20.1, JP3.1, Q3.3 (D), U3.3 (VBAT), X1.2
VBUS: CHG0.A, D4.A, JP3.3, Q3.1 (G), R4.2, U3.4 (VDD), X6.A4B9 (VBUS), X6.B4A9 (VBUS)
VHI: C1.1, C19.1, C21.1, D4.C, Q3.2 (S), R3.2, R18.2, R19.2, U2.1 (IN), X2.18 (+5V)
~RESET: IC1.26 (/RUN), JP1.16, R1.2, SW1.A, SW1.A' (P1)

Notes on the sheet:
10K = 100mA
USB AND BATTERY CHARGING
I2C Pullups & Shift
BREAKOUTS
NEOPIXEL
DVI OUTPUT
RP2040 BYPASS CAPS
POWER AND FILTERING
2.0K = 500mA
RED LED
USB TYPE C
RESET
1.0K = 1000mA
5.0K = 200mA
QSPI STORAGE

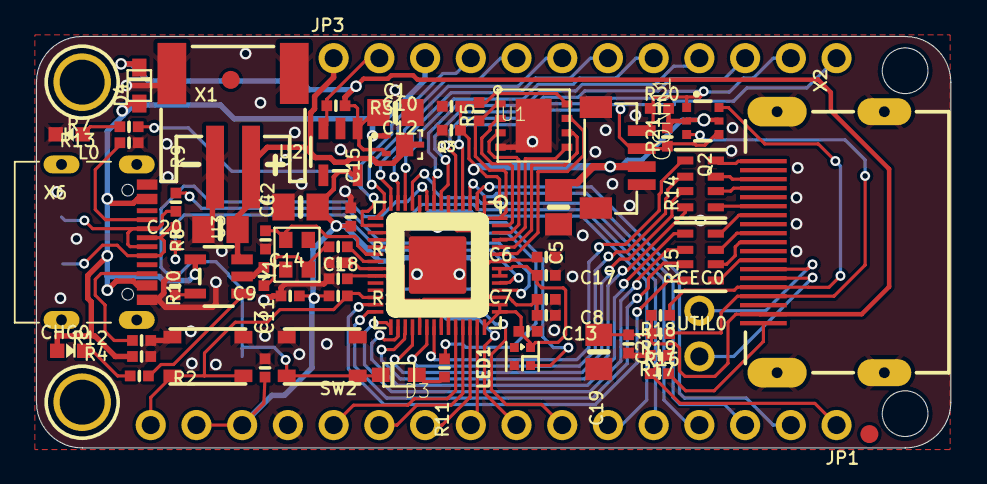
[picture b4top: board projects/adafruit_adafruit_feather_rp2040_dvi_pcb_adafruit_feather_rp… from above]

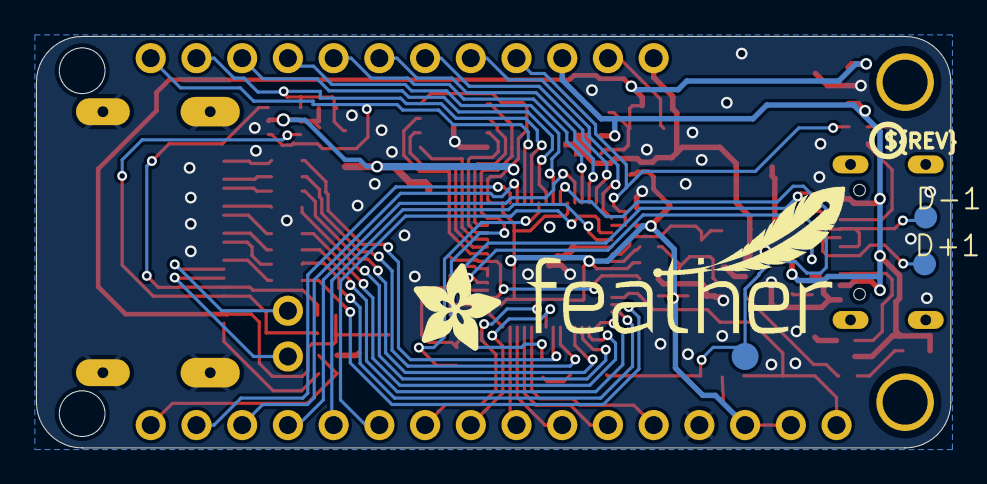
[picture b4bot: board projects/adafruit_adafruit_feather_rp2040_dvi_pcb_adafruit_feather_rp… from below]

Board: 2 copper layers, 50.8 x 22.9 mm, 143 parts (38 on the bottom side), 72 nets.

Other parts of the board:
@HOLE0, @HOLE1: (no value)
PLABEL0: PLABEL0
PLABEL1: PLABEL1
PLABEL2: PLABEL2
PLABEL3: PLABEL3
PLABEL4: PLABEL4
PLABEL5: PLABEL5
PLABEL6: PLABEL6
PLABEL7: PLABEL7
PLABEL8: PLABEL8
PLABEL9: PLABEL9
PLABEL10: PLABEL10
PLABEL11: PLABEL11
PLABEL12: PLABEL12
PLABEL13: PLABEL13
PLABEL14: PLABEL14
PLABEL15: PLABEL15
PLABEL16: PLABEL16
PLABEL17: PLABEL17
PLABEL18: PLABEL18
PLABEL19: PLABEL19
PLABEL20: PLABEL20
PLABEL21: PLABEL21
PLABEL22: PLABEL22
PLABEL23: PLABEL23
PLABEL24: PLABEL24
PLABEL25: PLABEL25
PLABEL26: PLABEL26
PLABEL27: PLABEL27
PLABEL28: PLABEL28
PLABEL29: PLABEL29
PLABEL30: PLABEL30
PLABEL31: PLABEL31
PLABEL32: PLABEL32
PLABEL33: PLABEL33
PLABEL34: PLABEL34
PLABEL35: PLABEL35
PLABEL36: PLABEL36
PLABEL37: PLABEL37
PLABEL38: PLABEL38
PLABEL39: PLABEL39
PLABEL40: PLABEL40
PLABEL41: PLABEL41
PLABEL42: PLABEL42
PLABEL43: PLABEL43
PLABEL44: PLABEL44
PLABEL45: PLABEL45
PLABEL46: PLABEL46
PLABEL47: PLABEL47
PLABEL48: PLABEL48
PLABEL49: PLABEL49
PLABEL50: PLABEL50
PLABEL51: PLABEL51
PLABEL52: PLABEL52
PLABEL53: PLABEL53
PLABEL54: PLABEL54
PLABEL55: PLABEL55
PLABEL56: PLABEL56
PLABEL57: PLABEL57
PLABEL58: PLABEL58
PLABEL59: PLABEL59
PLABEL60: PLABEL60
PLABEL61: PLABEL61
PLABEL62: PLABEL62
PLABEL63: PLABEL63
PLABEL64: PLABEL64
PLABEL65: PLABEL65
PLABEL66: PLABEL66
PLABEL67: PLABEL67
U$13: PCBFEAT-REV-040
U$42: FEATHERLOGO_MED
U$46: ADAFRUIT_5MM

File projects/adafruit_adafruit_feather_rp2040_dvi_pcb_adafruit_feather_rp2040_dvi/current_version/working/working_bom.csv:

"Id";"Designator";"Footprint";"Quantity";"Designation";"Supplier and ref";
1;"LED1";"SK6805_1515";1;"WS2812B_SK6805_1515";;;
2;"PLABEL25";"PLABEL25";1;"";;;
3;"PLABEL9";"PLABEL9";1;"";;;
4;"PLABEL23";"PLABEL23";1;"";;;
5;"C13,C18,C14,C6,C12,C9,C7";"_0402NO";7;"0.1uF";;;
6;"D3";"SOD-323F";1;"1N4148";;;
7;"PLABEL12";"PLABEL12";1;"";;;
8;"R20,R18,R3,R7,R19,R1,R2,R4,R5,R21";"_0402NO";10;"10K";;;
9;"R10,R9";"_0402NO";2;"22 ohm";;;
10;"C5,C1,C4,C20,C19";"0805-NO";5;"10uF";;;
11;"SW1,SW2";"BTN_RKB2_4.6X2.8";2;"KMR2";;;
12;"C10,C17,C11,C15,C21,C8";"_0402NO";6;"1uF";;;
13;"PLABEL22";"PLABEL22";1;"";;;
14;"PLABEL29";"PLABEL29";1;"";;;
15;"PLABEL30";"PLABEL30";1;"";;;
16;"PLABEL32";"PLABEL32";1;"";;;
17;"U$31,U$32";"MOUNTINGHOLE_2.5_PLATED";2;"MOUNTINGHOLE2.5";;;
18;"D4";"SOD-323F";1;"PMEG2020AEA";;;
19;"UTIL0,CEC0";"1X01_ROUND";2;"";;;
20;"PLABEL31";"PLABEL31";1;"";;;
21;"R14,R15";"RESPACK_4X0603";2;"220 Pack";;;
22;"PLABEL35";"PLABEL35";1;"";;;
23;"JP3";"1X12_ROUND";1;"";;;
24;"R8,R13,R12";"_0402NO";3;"5.1K";;;
25;"@HOLE0,@HOLE1";"";2;"";;;
26;"PLABEL27";"PLABEL27";1;"";;;
27;"PLABEL11";"PLABEL11";1;"";;;
28;"PLABEL4";"PLABEL4";1;"";;;
29;"U2";"SOT23-5";1;"RT9080-3.3";;;
30;"PLABEL5";"PLABEL5";1;"";;;
31;"PLABEL19";"PLABEL19";1;"";;;
32;"PLABEL28";"PLABEL28";1;"";;;
33;"PLABEL33";"PLABEL33";1;"";;;
34;"L0";"CHIPLED_0603_NOOUTLINE";1;"RED";;;
35;"PLABEL2";"PLABEL2";1;"";;;
36;"PLABEL3";"PLABEL3";1;"";;;
37;"PLABEL20";"PLABEL20";1;"";;;
38;"PLABEL34";"PLABEL34";1;"";;;
39;"PLABEL14";"PLABEL14";1;"";;;
40;"PLABEL17";"PLABEL17";1;"";;;
41;"R11,R6";"_0402NO";2;"1K";;;
42;"PLABEL0";"PLABEL0";1;"";;;
43;"C2,C3";"_0402NO";2;"22pF";;;
44;"R16,R17";"_0402NO";2;"100K";;;
45;"PLABEL13";"PLABEL13";1;"";;;
46;"PLABEL8";"PLABEL8";1;"";;;
47;"U$35,U$34";"FIDUCIAL_1MM";2;"FIDUCIAL_1MM";;;
48;"X2";"HDMI_MOLEX_47151-0001";1;"47151-0001";;;
49;"PLABEL1";"PLABEL1";1;"";;;
50;"PLABEL21";"PLABEL21";1;"";;;
51;"U3";"SOT23-5";1;"MCP73831T-2ACI/OT";;;
52;"CONN1";"JST_SH4_RA";1;"STEMMA_I2C_QTRA";;;
53;"Q2";"SOT363";1;"BSS138";;;
54;"Y1";"CRYSTAL_2.5X2";1;"12MHz/12pF";;;
55;"JP1";"1X16_ROUND";1;"";;;
56;"PLABEL15";"PLABEL15";1;"";;;
57;"Q3";"DFN2015-3";1;"DMG3415UFY";;;
58;"IC1";"QFN56_7MM_REDUCEDEPAD";1;"RP2040_QFN56";;;
59;"PLABEL24";"PLABEL24";1;"";;;
60;"PLABEL18";"PLABEL18";1;"";;;
61;"PLABEL6";"PLABEL6";1;"";;;
62;"PLABEL10";"PLABEL10";1;"";;;
63;"U1";"USON8_4X4";1;"8MB QSPI";;;
64;"PLABEL7";"PLABEL7";1;"";;;
65;"X6";"USB_C_CUSB31-CFM2AX-01-X";1;"USB Type C";;;
66;"PLABEL26";"PLABEL26";1;"";;;
67;"PLABEL16";"PLABEL16";1;"";;;
68;"X1";"JSTPH2_BATT";1;"JSTPH";;;
69;"CHG0";"CHIPLED_0603_NOOUTLINE";1;"ORANGE";;;
70;"PLABEL49";"PLABEL49";1;"";;;
71;"PLABEL59";"PLABEL59";1;"";;;
72;"PLABEL51";"PLABEL51";1;"";;;
73;"PLABEL40";"PLABEL40";1;"";;;
74;"PLABEL61";"PLABEL61";1;"";;;
75;"PLABEL44";"PLABEL44";1;"";;;
76;"PLABEL65";"PLABEL65";1;"";;;
77;"PLABEL58";"PLABEL58";1;"";;;
78;"PLABEL36";"PLABEL36";1;"";;;
79;"PLABEL67";"PLABEL67";1;"";;;
80;"U$42";"FEATHERLOGO_MED";1;"";;;
81;"PLABEL37";"PLABEL37";1;"";;;
82;"PLABEL56";"PLABEL56";1;"";;;
83;"PLABEL60";"PLABEL60";1;"";;;
84;"D+1,D-1";"B1,27";2;"TPB1,27";;;
85;"PLABEL66";"PLABEL66";1;"";;;
86;"PLABEL62";"PLABEL62";1;"";;;
87;"PLABEL45";"PLABEL45";1;"";;;
88;"PLABEL54";"PLABEL54";1;"";;;
89;"PLABEL48";"PLABEL48";1;"";;;
90;"PLABEL38";"PLABEL38";1;"";;;
91;"U$13";"PCBFEAT-REV-040";1;"";;;
92;"PLABEL42";"PLABEL42";1;"";;;
93;"U$46";"ADAFRUIT_5MM";1;"";;;
94;"PLABEL50";"PLABEL50";1;"";;;
95;"PLABEL57";"PLABEL57";1;"";;;
96;"TP3";"TESTPOINT_ROUND_1.5MM_NO";1;"";;;
97;"PLABEL55";"PLABEL55";1;"";;;
98;"PLABEL46";"PLABEL46";1;"";;;
99;"PLABEL64";"PLABEL64";1;"";;;
100;"PLABEL47";"PLABEL47";1;"";;;
101;"PLABEL53";"PLABEL53";1;"";;;
102;"PLABEL39";"PLABEL39";1;"";;;
103;"PLABEL52";"PLABEL52";1;"";;;
104;"PLABEL43";"PLABEL43";1;"";;;
105;"PLABEL63";"PLABEL63";1;"";;;
106;"PLABEL41";"PLABEL41";1;"";;;
